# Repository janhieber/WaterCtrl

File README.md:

WaterCtrl - Automatically water your flowers

# About
This project is a complete system to automatically
water your flowers. Yes, you can eventually go to holiday after years staying at home
because of your flowers.

Currently it is under development.
- The measure boards are finished.
- The main board is is in prototype stage.
- The Webinterface is nearly finished.
- The firmware development was just startet.

The idea is to measure the moisture of your flowser soil and
water them when needed. The watering is done according to moisture
or at a specific time intervall (for cactus).

The board will have a connector for a Raspberry Pi
which takes care of all high level functions like:
WLAN/LAN connection, webinterface, watering algorithm, weather station... 

The STM32 CPU will take care of the low level functions like:
watchdog for the rPi, PWM motor control, frequency measurement.

# Design
This is my idea of the device.

And this is the hardware design.

# Technical
Measure:
The moisture measurement is done by a oscillating circuit that uses two
big copper planes as capacitor in the soil.
When the soil is wet the capacity is high and the frequency will be low.

# More details
Please look in the subfolders for more informations,
nice pictures and other stuff.

# My future plans
I have some nice ideas, let me know what you think about this:

- The rPi will become the central control device with a radio module.
- Small sensor boards with a radio can interface a few sensors.
- Small motor control boards with a radio can control a few motors.
- The rPi, sensor and motor boards can be connected with wires when you don't want/need
  radio.
- Multiple sensor and motor boards can be used with one rPi. This way
  you can scale the system like you need it.

This will allow a complete modular system with most low level functions outsourced on
smaller modules and less long wires laying around.

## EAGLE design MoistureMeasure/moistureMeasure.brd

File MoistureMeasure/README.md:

Here are the Eagle 6.x schematics and board file for
the moistue measurement.

# Notes
The gray rectangle bottom left should be cut out to stick the
cable before spilling the board with epoxy.

# Nice pictures

")

# Order PCBs
For cheap PCBs you can order here:
http://dirtypcbs.com/
or here:
http://www.elecrow.com/services-pcb-prototyping-c-73_116.html

Because most people will [have to] order 5 or 10 pieces you can ask
me if someone as some PCBs left. If you have PCBs left, please tell me via Github
or mail: mail at janhieber dot net

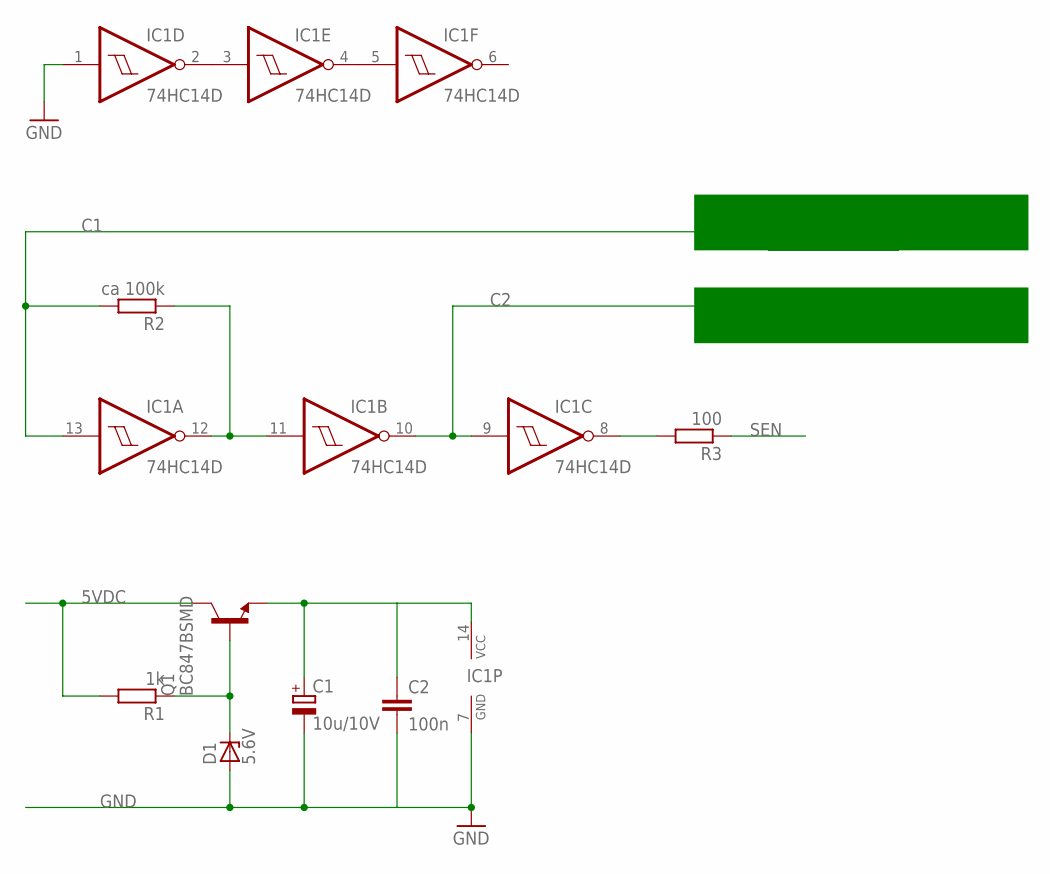
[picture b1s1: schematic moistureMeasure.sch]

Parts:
C1: 10u/10V; A/3216-18W
C2: 100n; C0805
D1: 5.6V; SOD80C
IC1: 74HC14D; SO14
Q1: BC847BSMD; SOT23
R1: 1k; R0805
R2: ca 100k; R0805
R3: 100; R0805

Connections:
5VDC: Q1.3 (C), R1.2
C1: IC1.13 (I), R2.2
C2: IC1.9 (I), IC1.10 (O)
GND: C1.-, C2.2, D1.A, IC1.1 (I), IC1.7 (GND)
unnamed: D1.C, Q1.1 (B), R1.1
unnamed: C1.+, C2.1, IC1.14 (VCC), Q1.2 (E)
unnamed: IC1.2 (O), IC1.3 (I)
unnamed: IC1.4 (O), IC1.5 (I)
unnamed: IC1.11 (I), IC1.12 (O), R2.1
unnamed: IC1.8 (O), R3.2
SEN: R3.1

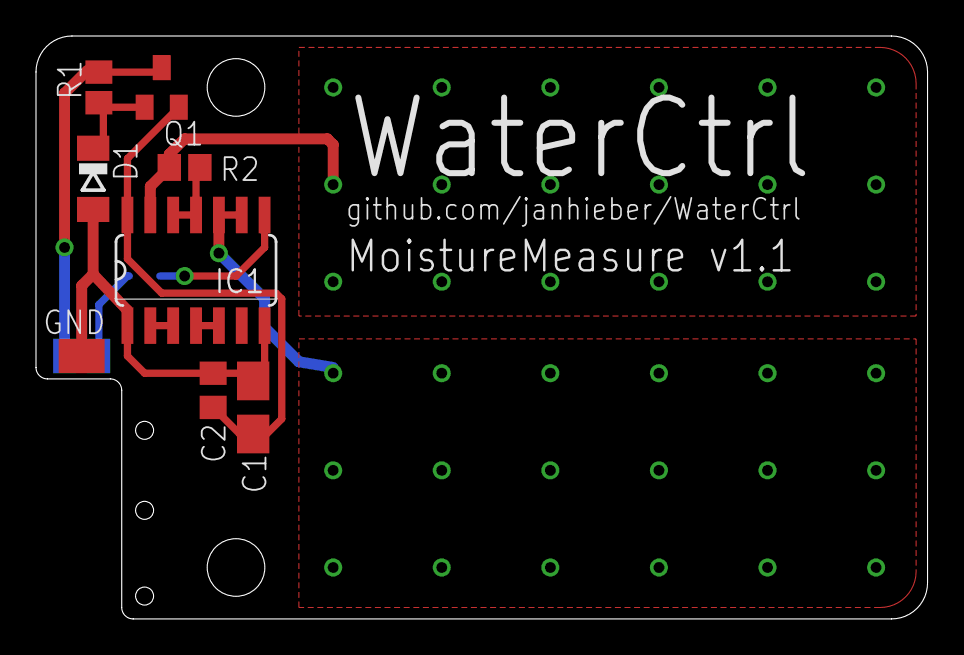
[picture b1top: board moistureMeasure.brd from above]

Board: 2 copper layers, 49.5 x 32.4 mm, 8 parts (1 on the bottom side), 10 nets.

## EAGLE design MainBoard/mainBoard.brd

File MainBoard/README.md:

News: First PCBs are ordered!

# Progress
First PCBs arrived!

# Info
This is the Eagle schematic/layout for the main board.

When I'm working on schematics or layout I'll update the
[schematic.pdf](https://github.com/janhieber/WaterCtrl/raw/master/MainBoard/docu/schematic.pdf) and
[board.png](https://github.com/janhieber/WaterCtrl/raw/master/MainBoard/docu/board.png) files.

Current layout

This is the STM32 board I have chosen for low level work.

It has a low power ARM Cortex M3 CPU running at max 72MHz.  
Should be enough for PWM and frequency measurement.  
It's very cheap (look on eBay) and has no useless peripherals.

# Order PCBs
For cheap PCBs you can order here: [http://dirtypcbs.com](http://dirtypcbs.com)

Because most people will [have to] order 5 or 10 pieces you can ask
me if someone has some PCBs left. If you have PCBs left, please tell me via Github Issue
or mail: mail at janhieber dot net

# Order parts
The parts are all from Reichelt (http://www.reichelt.de/) except the
STM32 board which I ordered on eBay.

Every part in the schematic has an attribute "R" with the Reichelt
part number as value.

To generate the BOM do the following:
 1. Open the schematic in Eagle
 2. File > Export > BOM
 3. Select "values" as list type

Now, Reichelt expects a CSV file with the following format:  
> DIODE GN;2  
> SMD 0805 100K;12

If you are working on Linux or Mac OSX you can execute this in a terminal:  
```bash
tail -n +2 BOM.csv | sed 's/\"//g' | awk -F ';' 'length($11)>0{print $11";"$1}' > BOM_reichelt.csv
```

*make sure you are in the directory where the BOM.csv is*

Otherwise use Libreoffice or Excel etc to generate the list, or add everything
manually to cart.

Now register at Reichelt and login.  
Click on your username on top and then "load cart" to import the CSV.

# ToDo
- [ ] Circuit for the moisture measurement (connectors, demultiplexer)
  - [x] schematic
  - [x] routed
  - [ ] tested
- [ ] Circuit for the water pump controlling (FETs ...)
  - [x] schematic
  - [x] routed
  - [ ] tested
- [x] Power supply circuit for 5V
  - [x] schematic
  - [x] routed
  - [x] tested
- [ ] Wiring up the STM32 and rPi
  - [x] schematic
  - [x] routed
  - [ ] SPI connection
  - [ ] tested

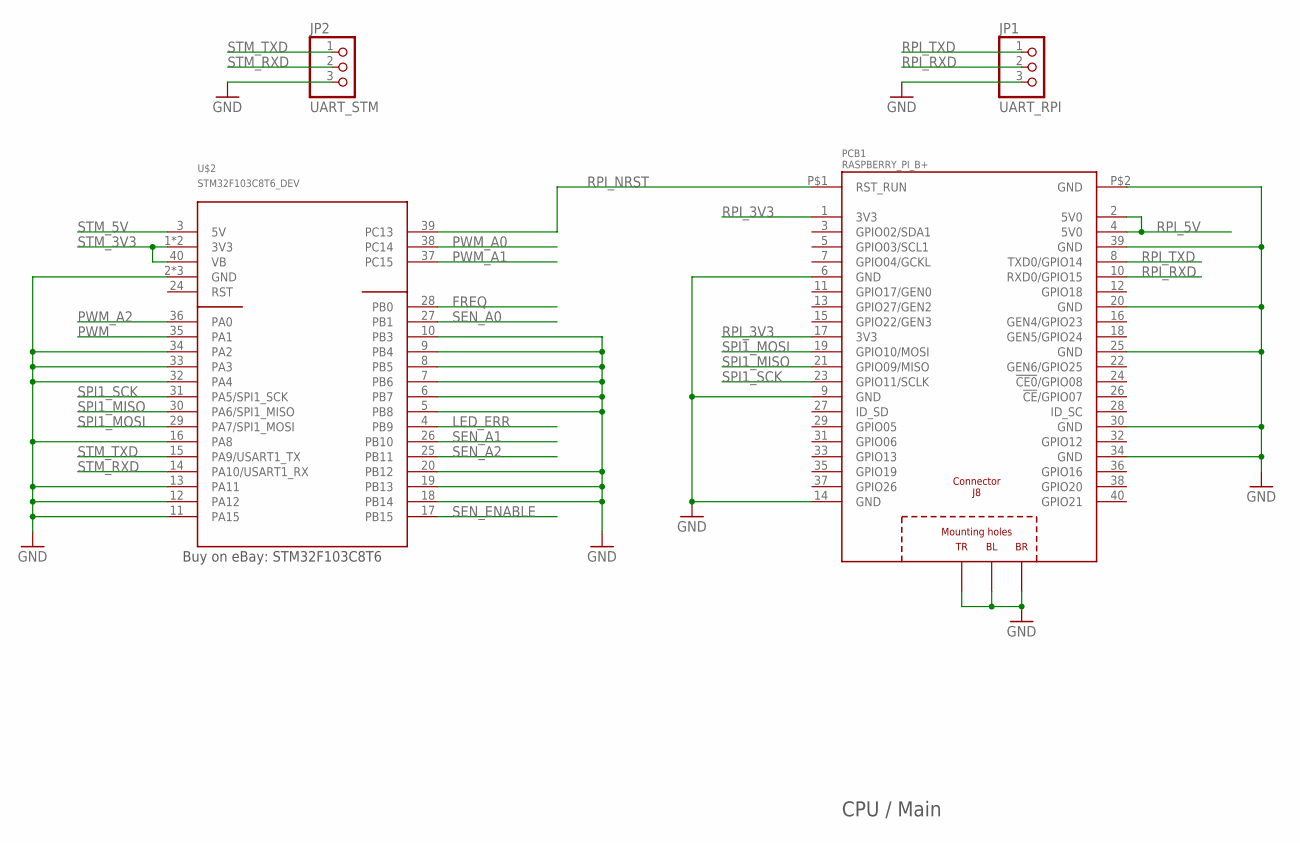
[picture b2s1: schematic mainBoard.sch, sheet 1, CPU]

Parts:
JP1: UART_RPI; 1X03
JP2: UART_STM; 1X03
PCB1: RASPBERRY_PI_B+; RASPBERRY_PI_BPLUS_TPLACE_SMD_MIRR
U$2: STM32F103C8T6_DEV; STM32F103C8T6_DEV_SMD

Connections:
FREQ: U$2.28 (PB0); also elsewhere on the board
GND: JP1.3, JP2.3, PCB1.6 (GND), PCB1.9 (GND), PCB1.14 (GND), PCB1.20 (GND), PCB1.25 (GND), PCB1.30 (GND), PCB1.34 (GND), PCB1.39 (GND), PCB1.P$2 (GND), PCB1.PE_BL (BL), PCB1.PE_BR (BR), PCB1.PE_TR (TR), U$2.2 (GND), U$2.5 (PB8), U$2.6 (PB7), U$2.7 (PB6), U$2.8 (PB5), U$2.9 (PB4), U$2.10 (PB3), U$2.11 (PA15), U$2.12 (PA12), U$2.13 (PA11), U$2.16 (PA8), U$2.18 (PB14), U$2.19 (PB13), U$2.20 (PB12), U$2.21 (GND), U$2.22 (GND), U$2.32 (PA4), U$2.33 (PA3), U$2.34 (PA2); also elsewhere on the board
LED_ERR: U$2.4 (PB9); also elsewhere on the board
PWM: U$2.35 (PA1); also elsewhere on the board
PWM_A0: U$2.38 (PC14); also elsewhere on the board
PWM_A1: U$2.37 (PC15); also elsewhere on the board
PWM_A2: U$2.36 (PA0); also elsewhere on the board
RPI_3V3: PCB1.1 (3V3), PCB1.17 (3V3); also elsewhere on the board
RPI_5V: PCB1.2 (5V0), PCB1.4 (5V0); also elsewhere on the board
RPI_NRST: PCB1.P$1 (RST_RUN), U$2.39 (PC13)
RPI_RXD: JP1.2, PCB1.10 (RXD0/GPIO15)
RPI_TXD: JP1.1, PCB1.8 (TXD0/GPIO14)
SEN_A0: U$2.27 (PB1); also elsewhere on the board
SEN_A1: U$2.26 (PB10); also elsewhere on the board
SEN_A2: U$2.25 (PB11); also elsewhere on the board
SEN_ENABLE: U$2.17 (PB15); also elsewhere on the board
SPI1_MISO: PCB1.21 (GPIO09/MISO), U$2.30 (PA6/SPI1_MISO)
SPI1_MOSI: PCB1.19 (GPIO10/MOSI), U$2.29 (PA7/SPI1_MOSI)
SPI1_SCK: PCB1.23 (GPIO11/SCLK), U$2.31 (PA5/SPI1_SCK)
STM_3V3: U$2.1 (3V3), U$2.23 (3V3), U$2.40 (VB); also elsewhere on the board
STM_5V: U$2.3 (5V); also elsewhere on the board
STM_RXD: JP2.2, U$2.14 (PA10/USART1_RX)
STM_TXD: JP2.1, U$2.15 (PA9/USART1_TX)

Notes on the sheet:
CPU / Main
Buy on eBay: STM32F103C8T6

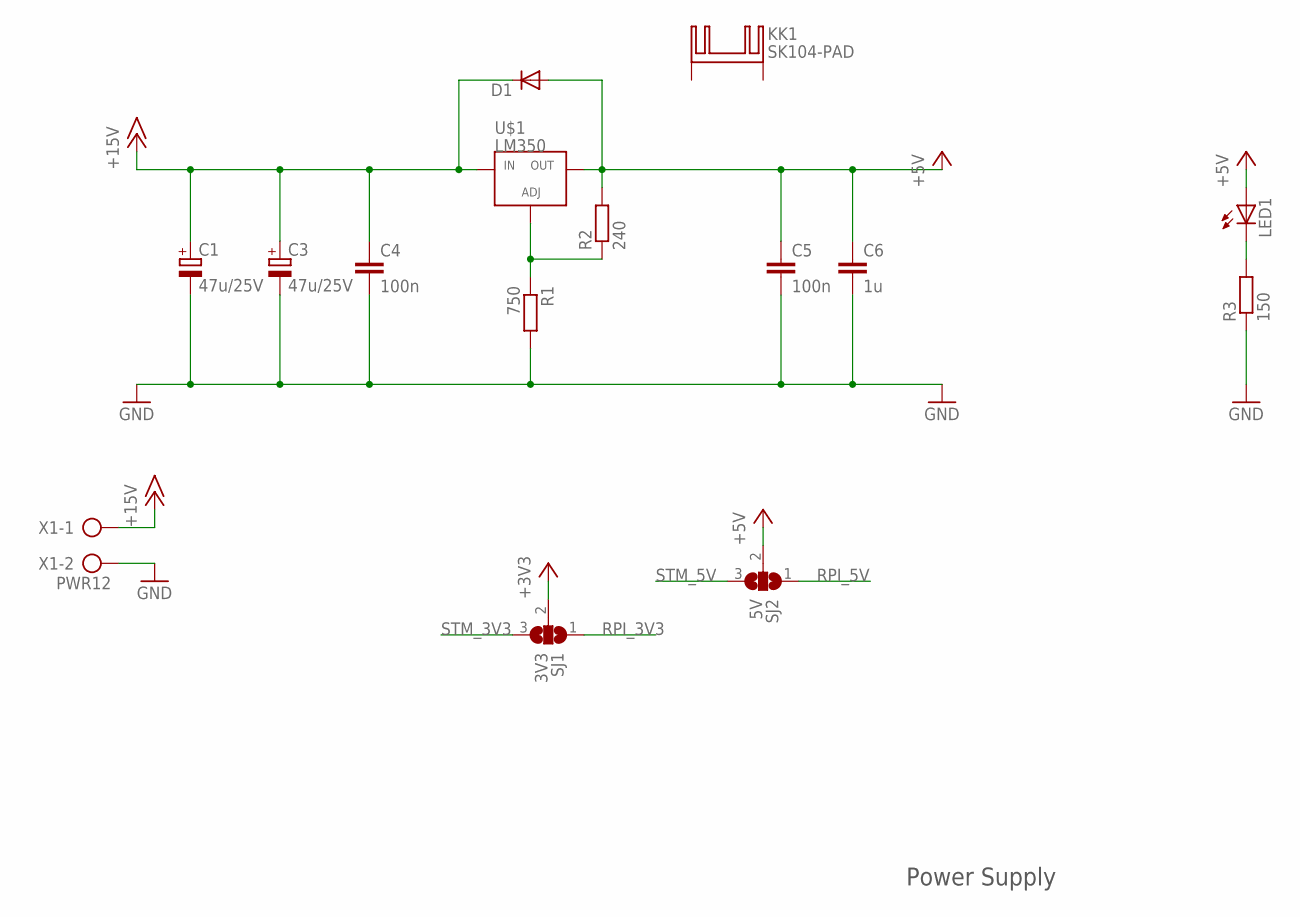
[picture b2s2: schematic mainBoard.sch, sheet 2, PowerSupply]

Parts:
C1, C3: 47u/25V; PANASONIC_D
C4, C5: 100n; C0805
C6: 1u; C0805
D1: DIODE-MELF-MLL41; MELF-MLL41
KK1: SK104-PAD
LED1: LEDCHIP-LED0805; CHIP-LED0805
R1: 750; R0805
R2: 240; R0805
R3: 150; R0805
SJ1: 3V3; SJ_2
SJ2: 5V; SJ_2
U$1: LM350; TO220
X1: PWR12; AK500/2

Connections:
+3V3: SJ1.2; also elsewhere on the board
+5V: C5.1, C6.1, D1.A, LED1.A, R2.2, SJ2.2, U$1.2 (OUT)
+15V: C1.+, C3.+, C4.1, D1.C, U$1.3 (IN), X1.1; also elsewhere on the board
GND: C1.-, C3.-, C4.2, C5.2, C6.2, R1.2, R3.1, X1.2; also elsewhere on the board
unnamed: LED1.C, R3.2
unnamed: R1.1, R2.1, U$1.1 (ADJ)
RPI_3V3: SJ1.1; also elsewhere on the board
RPI_5V: SJ2.1; also elsewhere on the board
STM_3V3: SJ1.3; also elsewhere on the board
STM_5V: SJ2.3; also elsewhere on the board

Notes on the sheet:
Power Supply

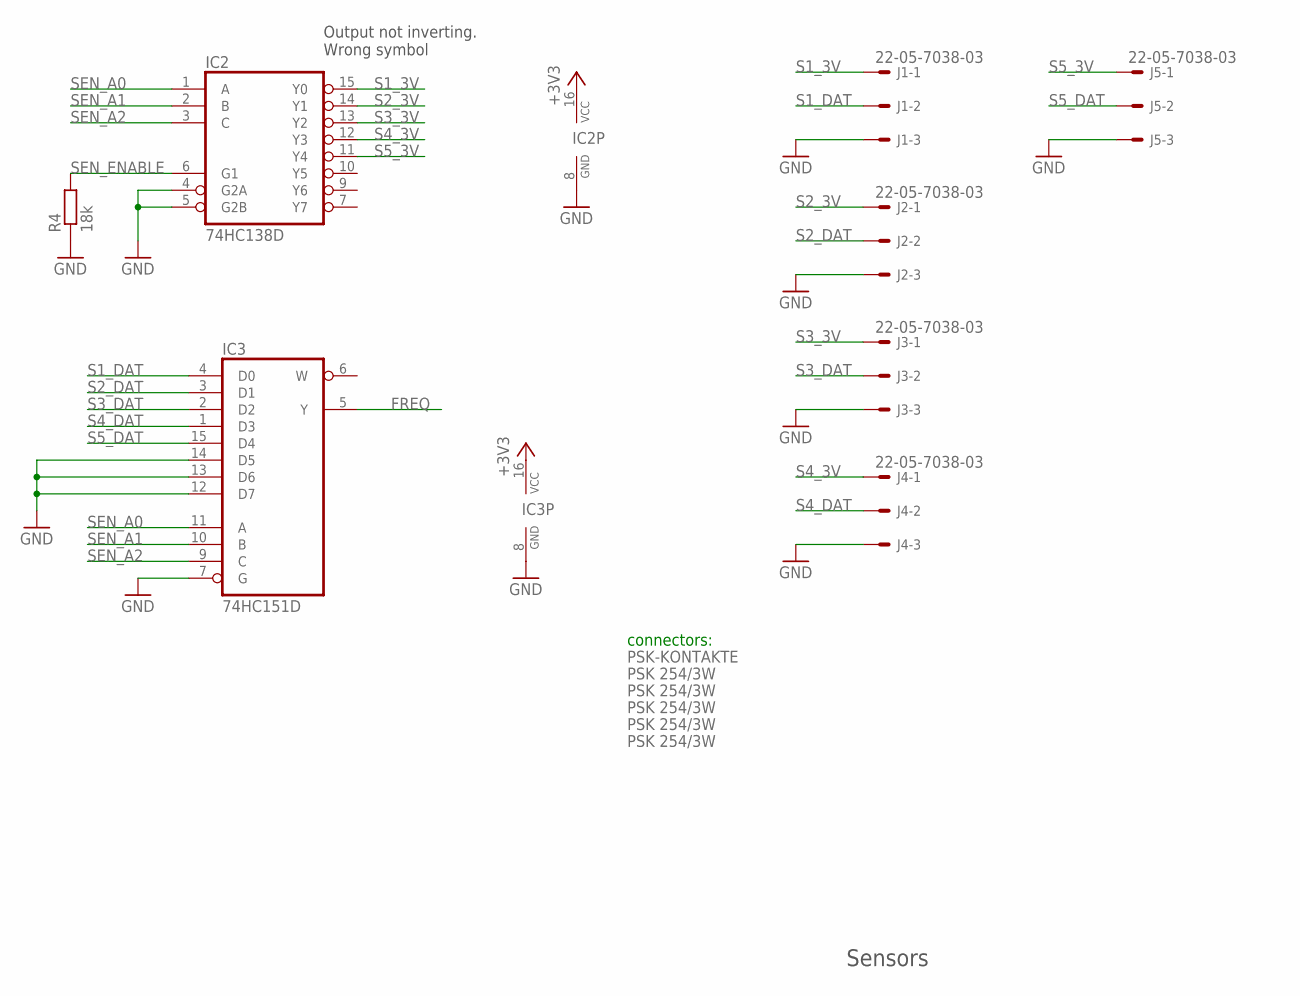
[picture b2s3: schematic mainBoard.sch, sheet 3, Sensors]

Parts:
IC2: 74HC138D; SO16
IC3: 74HC151D; SO16
J1, J2, J3, J4, J5: 22-05-7038-03; 7395-03
R4: 18k; R0805
U$3, U$4, U$5, U$6, U$7: PSK 254/3W; DUMMY_BOM
U$8: PSK-KONTAKTE; DUMMY_BOM

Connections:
+3V3: IC2.16 (VCC), IC3.16 (VCC); also elsewhere on the board
FREQ: IC3.5 (Y); also elsewhere on the board
GND: IC2.4 (G2A), IC2.5 (G2B), IC2.8 (GND), IC3.7 (G), IC3.8 (GND), IC3.12 (D7), IC3.13 (D6), IC3.14 (D5), J1.3, J2.3, J3.3, J4.3, J5.3, R4.1; also elsewhere on the board
S1_3V: IC2.15 (Y0), J1.1
S1_DAT: IC3.4 (D0), J1.2
S2_3V: IC2.14 (Y1), J2.1
S2_DAT: IC3.3 (D1), J2.2
S3_3V: IC2.13 (Y2), J3.1
S3_DAT: IC3.2 (D2), J3.2
S4_3V: IC2.12 (Y3), J4.1
S4_DAT: IC3.1 (D3), J4.2
S5_3V: IC2.11 (Y4), J5.1
S5_DAT: IC3.15 (D4), J5.2
SEN_A0: IC2.1 (A), IC3.11 (A); also elsewhere on the board
SEN_A1: IC2.2 (B), IC3.10 (B); also elsewhere on the board
SEN_A2: IC2.3 (C), IC3.9 (C); also elsewhere on the board
SEN_ENABLE: IC2.6 (G1), R4.2; also elsewhere on the board

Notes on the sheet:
Output not inverting. Wrong symbol
connectors:
Sensors

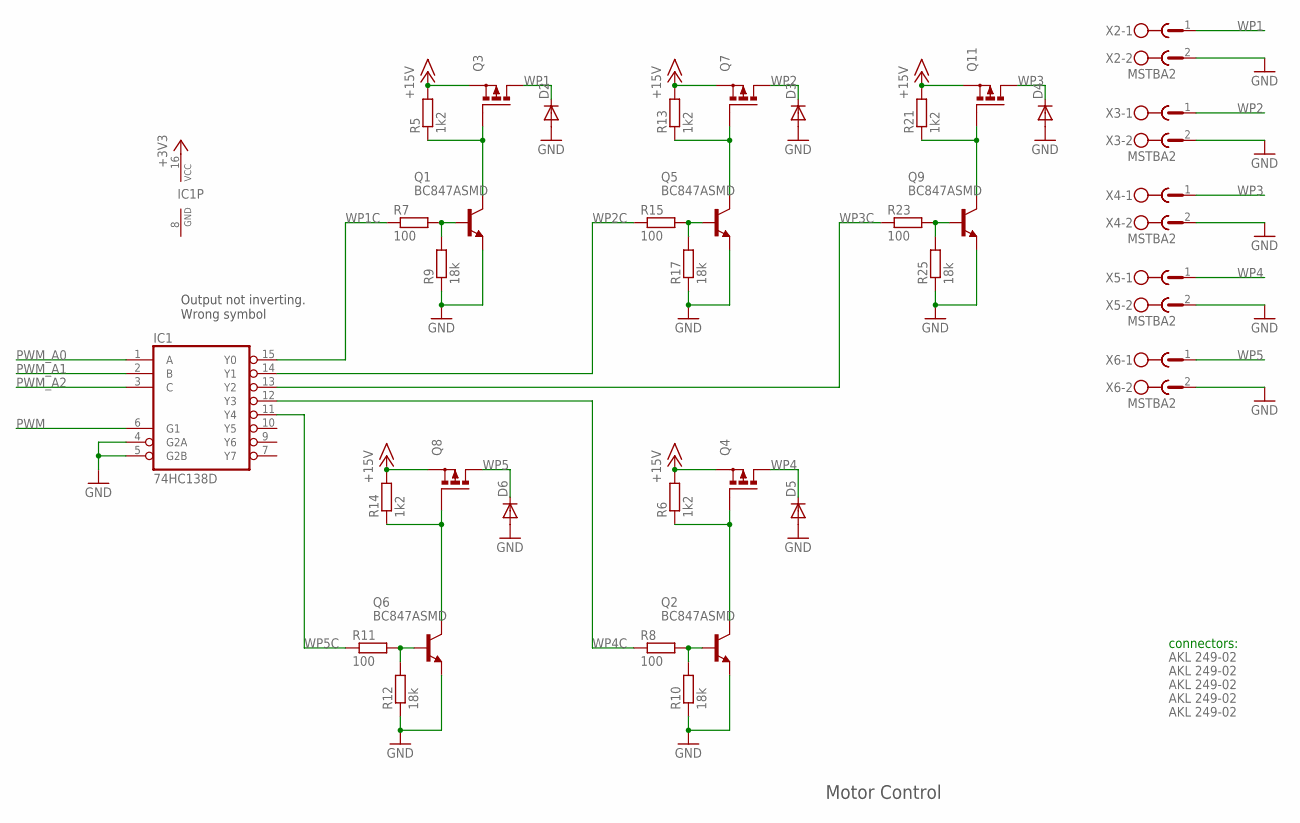
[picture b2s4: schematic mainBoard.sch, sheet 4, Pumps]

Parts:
D2, D3, D4, D5, D6: DIODE-DO-214AC; DO-214AC
IC1: 74HC138D; SO16
Q1, Q2, Q5, Q6, Q9: BC847ASMD; SOT23
Q3, Q4, Q7, Q8, Q11: P-MOSFET-SO8; SO-08
R5, R6, R13, R14, R21: 1k2; R0805
R7, R8, R11, R15, R23: 100; R0805
R9, R10, R12, R17, R25: 18k; R0805
U$9, U$10, U$11, U$12, U$13: AKL 249-02; DUMMY_BOM
X2, X3, X4, X5, X6: MSTBA2

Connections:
+3V3: IC1.16 (VCC); also elsewhere on the board
+15V: Q3.1 (S), Q3.2 (S), Q3.3 (S), Q4.1 (S), Q4.2 (S), Q4.3 (S), Q7.1 (S), Q7.2 (S), Q7.3 (S), Q8.1 (S), Q8.2 (S), Q8.3 (S), Q11.1 (S), Q11.2 (S), Q11.3 (S), R5.2, R6.2, R13.2, R14.2, R21.2; also elsewhere on the board
GND: D2.A, D3.A, D4.A, D5.A, D6.A, IC1.4 (G2A), IC1.5 (G2B), IC1.8 (GND), Q1.2 (E), Q2.2 (E), Q5.2 (E), Q6.2 (E), Q9.2 (E), R9.1, R10.1, R12.1, R17.1, R25.1, X2.2, X3.2, X4.2, X5.2, X6.2; also elsewhere on the board
unnamed: Q5.3 (C), Q7.4 (G), R13.1
unnamed: Q1.3 (C), Q3.4 (G), R5.1
unnamed: Q6.3 (C), Q8.4 (G), R14.1
unnamed: Q1.1 (B), R7.2, R9.2
unnamed: Q6.1 (B), R11.2, R12.2
unnamed: Q5.1 (B), R15.2, R17.2
unnamed: Q9.3 (C), Q11.4 (G), R21.1
unnamed: Q9.1 (B), R23.2, R25.2
unnamed: Q2.3 (C), Q4.4 (G), R6.1
unnamed: Q2.1 (B), R8.2, R10.2
PWM: IC1.6 (G1); also elsewhere on the board
PWM_A0: IC1.1 (A); also elsewhere on the board
PWM_A1: IC1.2 (B); also elsewhere on the board
PWM_A2: IC1.3 (C); also elsewhere on the board
WP1: D2.C, Q3.5 (D), Q3.6 (D), Q3.7 (D), Q3.8 (D), X2.1
WP1C: IC1.15 (Y0), R7.1
WP2: D3.C, Q7.5 (D), Q7.6 (D), Q7.7 (D), Q7.8 (D), X3.1
WP2C: IC1.14 (Y1), R15.1
WP3: D4.C, Q11.5 (D), Q11.6 (D), Q11.7 (D), Q11.8 (D), X4.1
WP3C: IC1.13 (Y2), R23.1
WP4: D5.C, Q4.5 (D), Q4.6 (D), Q4.7 (D), Q4.8 (D), X5.1
WP4C: IC1.12 (Y3), R8.1
WP5: D6.C, Q8.5 (D), Q8.6 (D), Q8.7 (D), Q8.8 (D), X6.1
WP5C: IC1.11 (Y4), R11.1

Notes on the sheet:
Motor Control
connectors:
Output not inverting. Wrong symbol

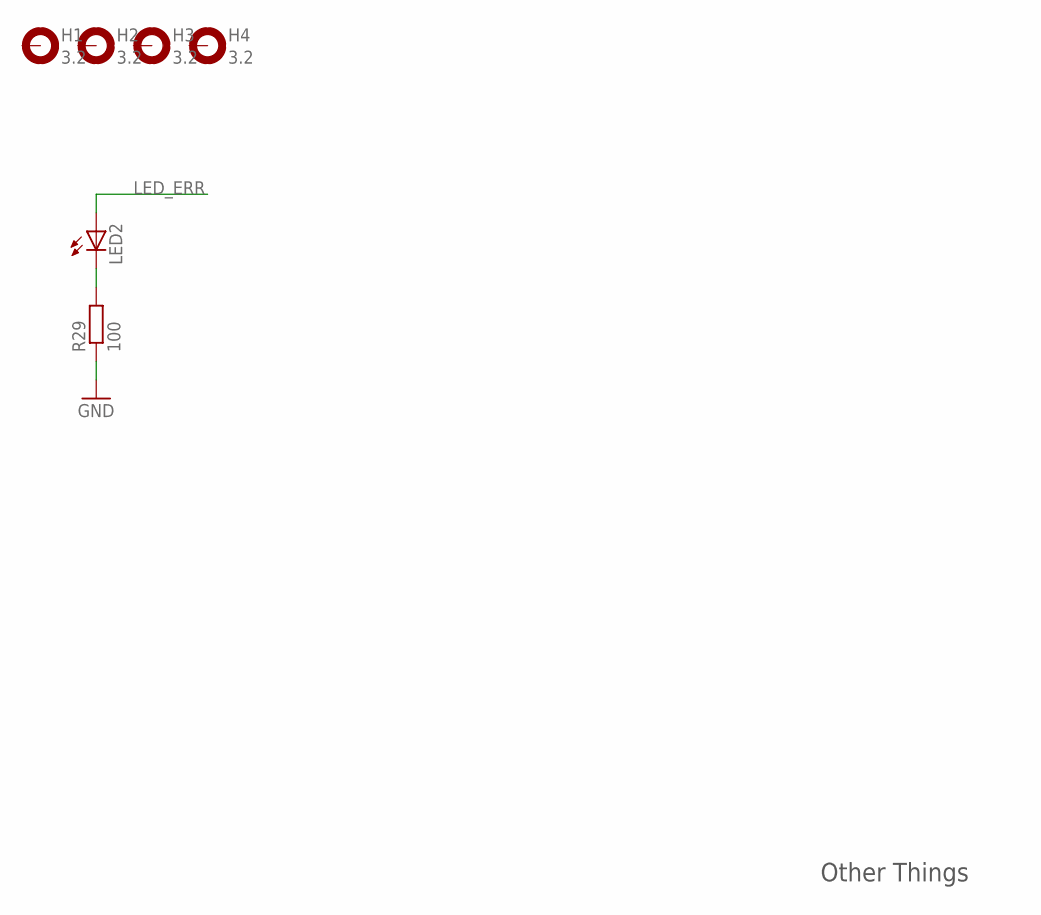
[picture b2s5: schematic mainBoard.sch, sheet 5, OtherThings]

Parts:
H1, H2, H3, H4: 3.2; 3,2-PAD
LED2: LED3MM
R29: 100; R0805

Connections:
GND: R29.1; also elsewhere on the board
LED_ERR: LED2.A; also elsewhere on the board
unnamed: LED2.K (C), R29.2

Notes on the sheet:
Other Things

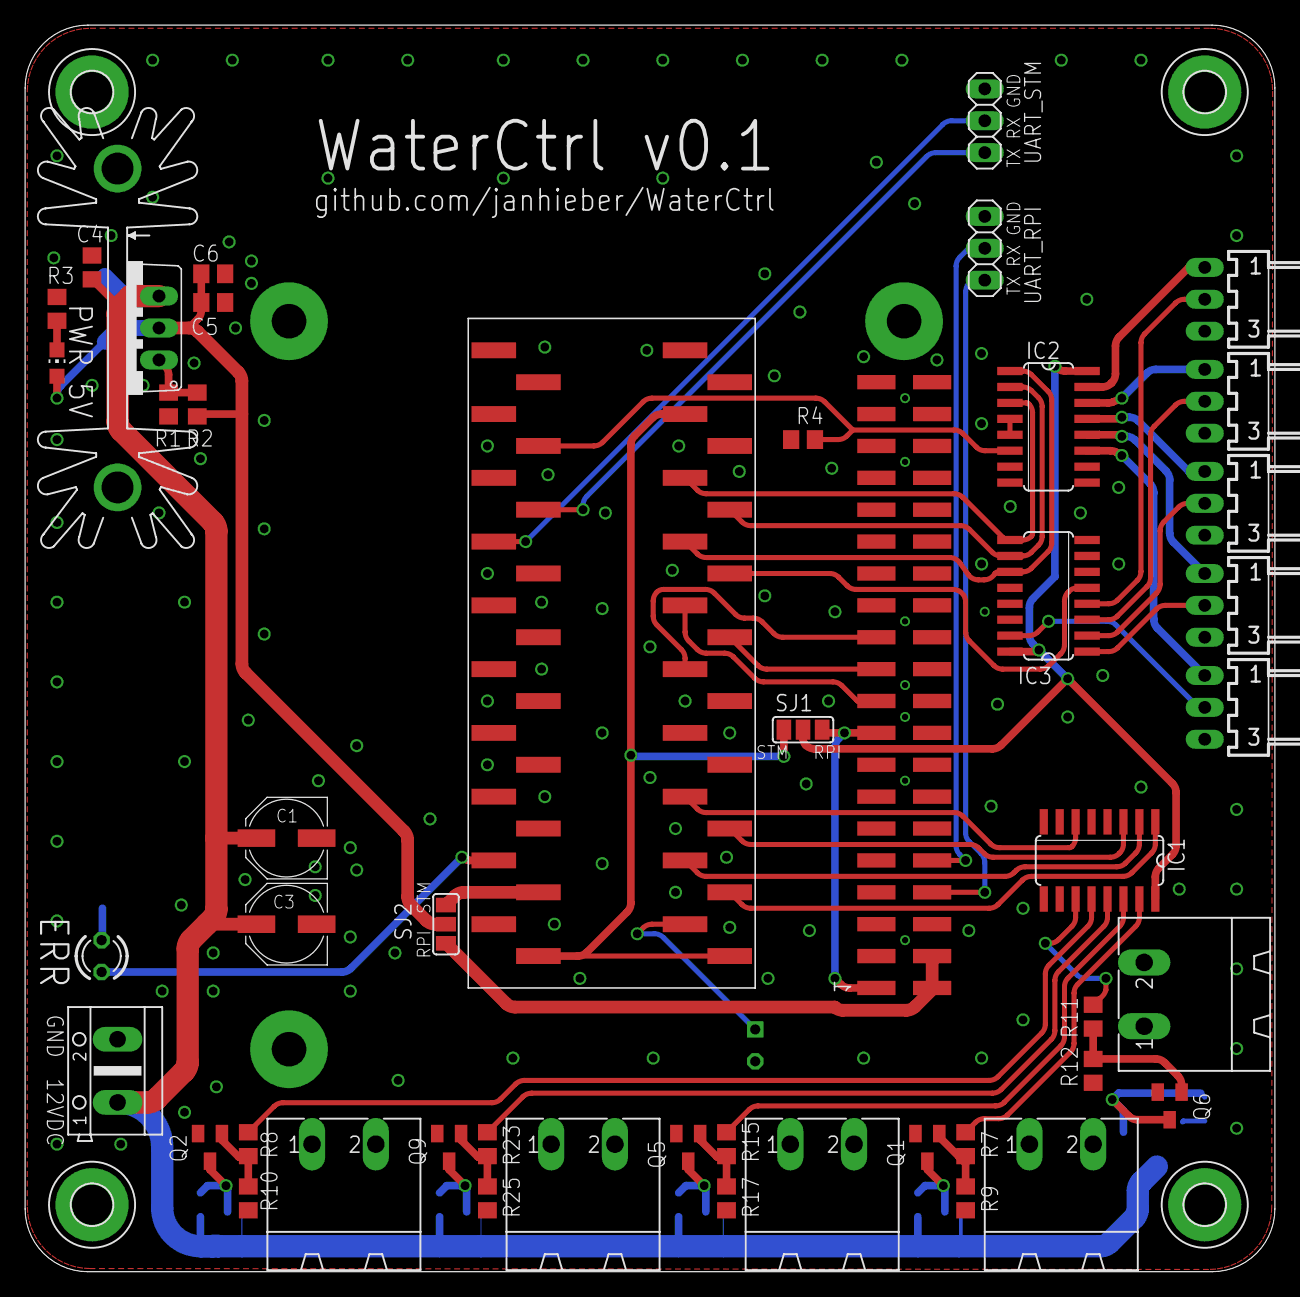
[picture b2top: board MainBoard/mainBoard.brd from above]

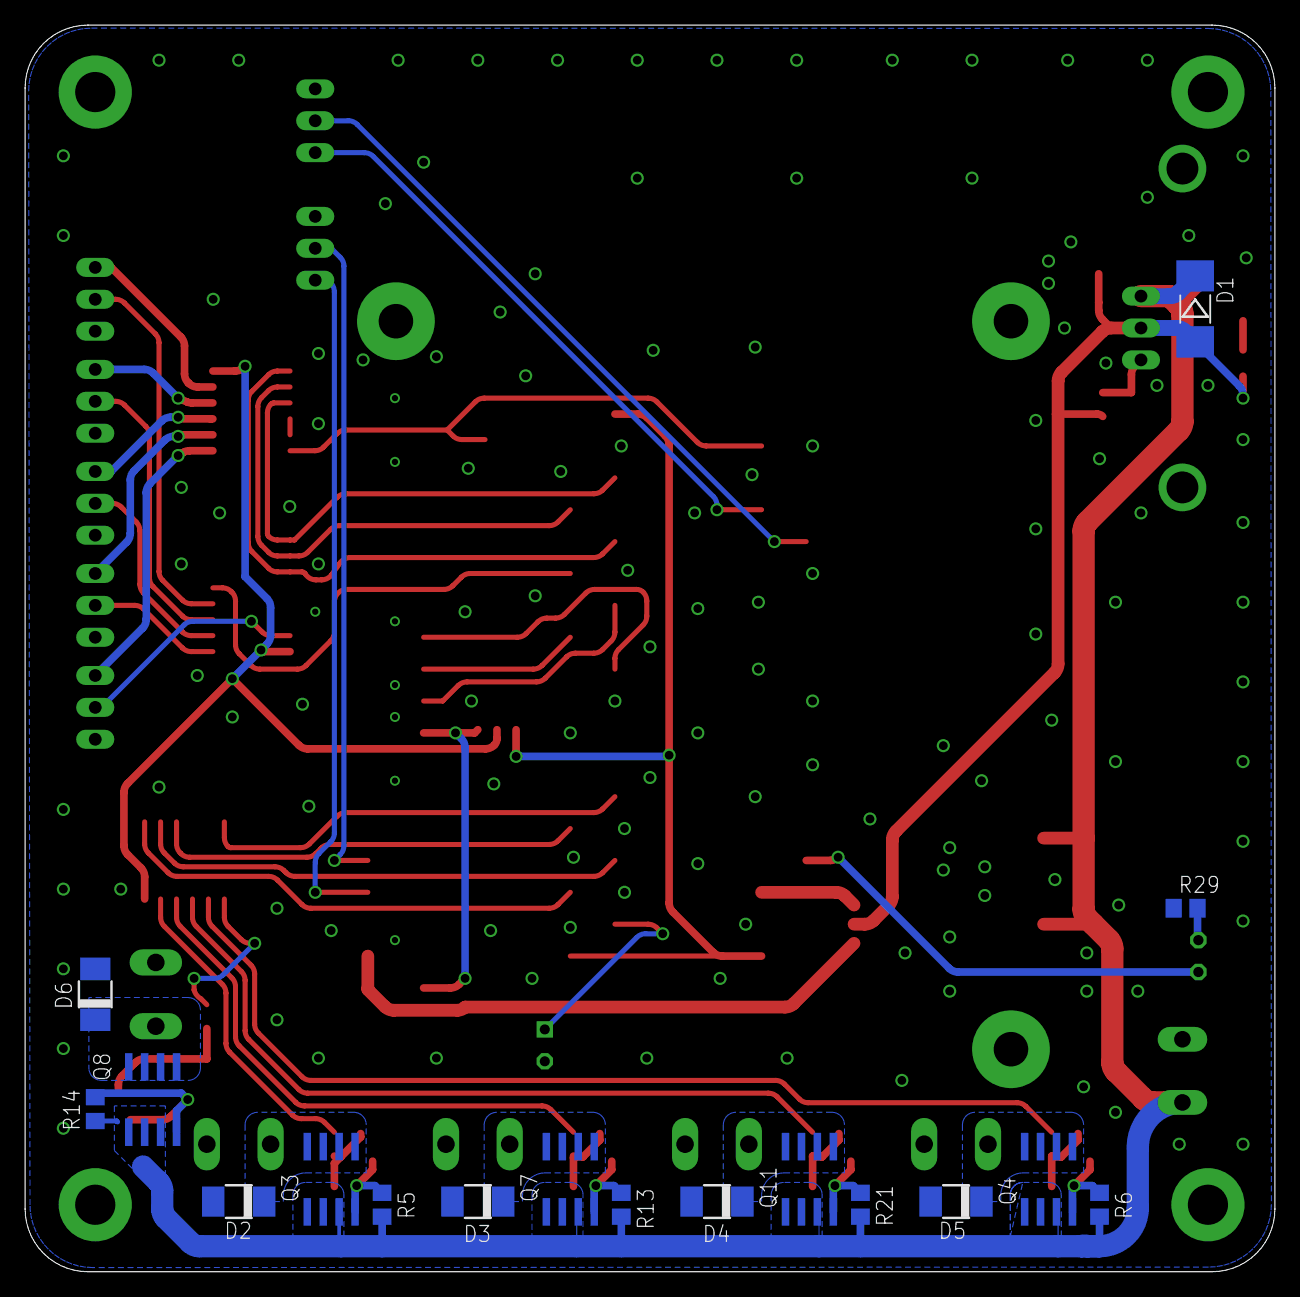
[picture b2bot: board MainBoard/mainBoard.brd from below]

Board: 2 copper layers, 99.6 x 99.3 mm, 80 parts (17 on the bottom side), 59 nets.

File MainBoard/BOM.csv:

"Qty";"Value";"Device";"Package";"Parts";"Description";"MF";"MPN";"OC_FARNELL";"OC_NEWARK";"R";
"5";"";"DIODE-DO-214AC";"DO-214AC";"D2, D3, D4, D5, D6";"DIODE";"";"";"";"";"B 140 F";
"1";"";"DIODE-MELF-MLL41";"MELF-MLL41";"D1";"DIODE";"";"";"";"";"1N 4002 SMD";
"1";"";"LED3MM";"LED3MM";"LED2";"LED";"";"";"";"";"SLK 3MM RT";
"1";"";"LEDCHIP-LED0805";"CHIP-LED0805";"LED1";"LED";"";"";"";"";"SMD-LED 0805 GN";
"5";"";"P-MOSFET-SO8";"SO-08";"Q3, Q4, Q7, Q8, Q11";"P-Channel MOSFET";"";"";"";"";"IRF 9332";
"6";"100";"R-EU_R0805";"R0805";"R7, R8, R11, R15, R23, R29";"RESISTOR, European symbol";"";"";"";"";"SMD-0805 100";
"2";"100n";"C-EUC0805";"C0805";"C4, C5";"CAPACITOR, European symbol";"";"";"";"";"X7R-G0805 100N";
"1";"150";"R-EU_R0805";"R0805";"R3";"RESISTOR, European symbol";"";"";"";"";"SMD-0805 150";
"6";"18k";"R-EU_R0805";"R0805";"R4, R9, R10, R12, R17, R25";"RESISTOR, European symbol";"";"";"";"";"SMD-0805 18,0K";
"5";"1k2";"R-EU_R0805";"R0805";"R5, R6, R13, R14, R21";"RESISTOR, European symbol";"";"";"";"";"SMD-0805 1,20K";
"1";"1u";"C-EUC0805";"C0805";"C6";"CAPACITOR, European symbol";"";"";"";"";"X7R-G0805 1,0/25";
"5";"22-05-7038-03";"22-05-7038-03";"7395-03";"J1, J2, J3, J4, J5";"CONNECTOR";"";"";"unknown";"unknown";"PSS 254/3W";
"1";"240";"R-EU_R0805";"R0805";"R2";"RESISTOR, European symbol";"";"";"";"";"SPR-0805 240";
"4";"3.2";"MOUNT-PAD-ROUND3.2";"3,2-PAD";"H1, H2, H3, H4";"MOUNTING PAD, round";"";"";"";"";"";
"1";"3V3";"SJ2W";"SJ_2";"SJ1";"SMD solder JUMPER";"";"";"";"";"";
"2";"47u/25V";"CPOL-EUD";"PANASONIC_D";"C1, C3";"POLARIZED CAPACITOR, European symbol";"";"";"";"";"VF 47/25 P-D";
"1";"5V";"SJ2W";"SJ_2";"SJ2";"SMD solder JUMPER";"";"";"";"";"";
"2";"74HC138D";"74HC138D";"SO16";"IC1, IC2";"3-line to 8-line DECODER/DEMULTIPLEXER";"";"";"";"";"SMD HC 238";
"1";"74HC151D";"74HC151D";"SO16";"IC3";"Data SELECTOR/MULTIPLEXER";"";"";"";"";"SMD HC 151";
"1";"750";"R-EU_R0805";"R0805";"R1";"RESISTOR, European symbol";"";"";"";"";"SPR-0805 750";
"5";"AKL 249-02";"DUMMY_BOM";"DUMMY_BOM";"U$9, U$10, U$11, U$12, U$13";"";"";"";"";"";"AKL 249-02";
"5";"BC847ASMD";"BC847ASMD";"SOT23";"Q1, Q2, Q5, Q6, Q9";"NPN Transistor";"";"";"";"";"BC 847A SMD";
"1";"LM350";"LM350";"TO220";"U$1";"";"";"";"";"";"LM 350-220";
"5";"MSTBA2";"MSTBA2";"MSTBA2";"X2, X3, X4, X5, X6";"PHOENIX";"FARNELL";"1757242";"3705171";"71C4161";"AKL 230-02";
"5";"PSK 254/3W";"DUMMY_BOM";"DUMMY_BOM";"U$3, U$4, U$5, U$6, U$7";"";"";"";"";"";"PSK 254/3W";
"1";"PSK-KONTAKTE";"DUMMY_BOM";"DUMMY_BOM";"U$8";"";"";"";"";"";"PSK-KONTAKTE";
"1";"PWR12";"AK500/2";"AK500/2";"X1";"CONNECTOR";"";"";"unknown";"unknown";"AKL 101-02";
"1";"RASPBERRY_PI_B+";"RASPBERRY_PI_B+";"RASPBERRY_PI_BPLUS_TPLACE_SMD_MIRR";"PCB1";"Raspberry Pi B+";"";"";"";"";"";
"1";"SK104-PAD";"SK104-PAD";"SK104-PAD";"KK1";"HEATSINK manufacturer Fischer/distributor Buerklin";"";"";"";"";"";
"1";"STM32F103C8T6_DEV";"STM32F103C8T6_DEV";"STM32F103C8T6_DEV_SMD";"U$2";"";"";"";"";"";"";
"1";"UART_RPI";"PINHD-1X3";"1X03";"JP1";"PIN HEADER";"";"";"";"";"MPE 087-1-003";
"1";"UART_STM";"PINHD-1X3";"1X03";"JP2";"PIN HEADER";"";"";"";"";"MPE 087-1-003";

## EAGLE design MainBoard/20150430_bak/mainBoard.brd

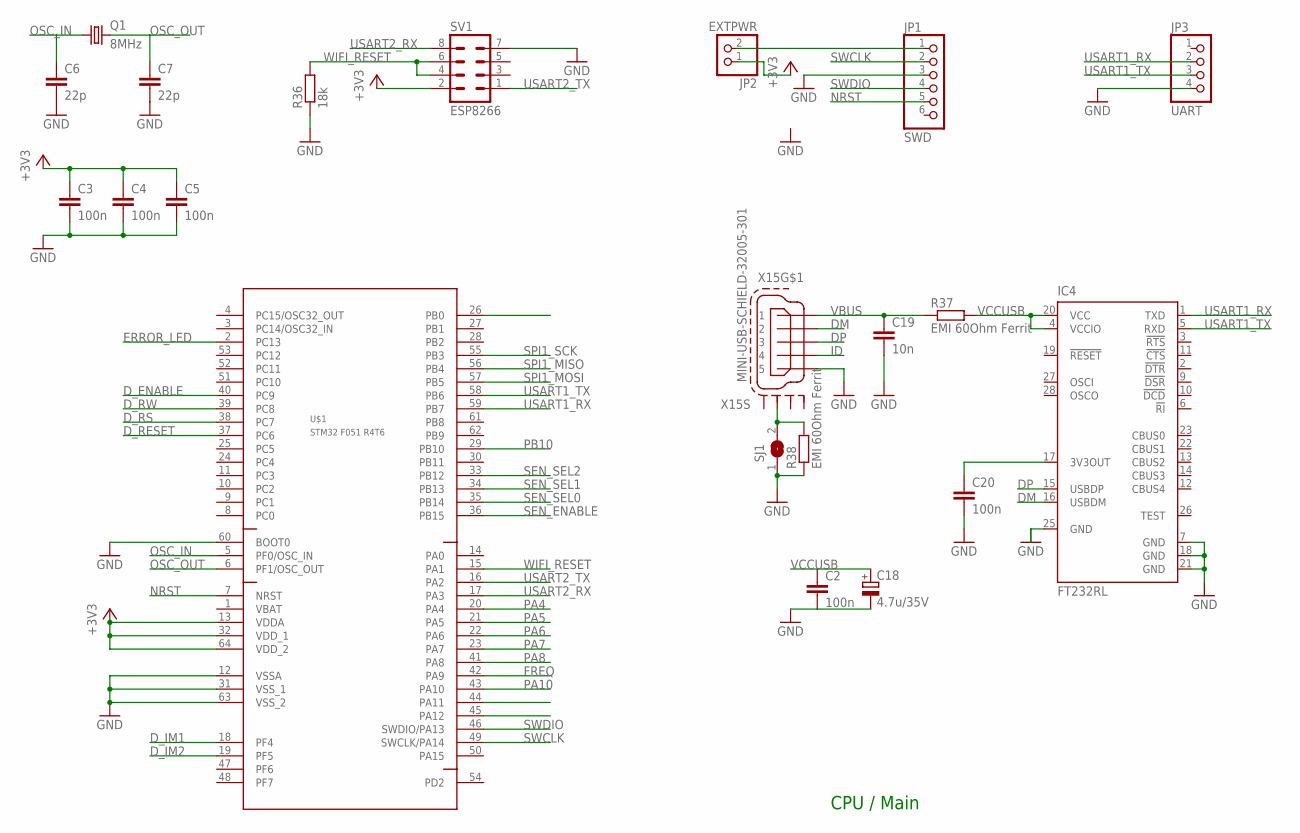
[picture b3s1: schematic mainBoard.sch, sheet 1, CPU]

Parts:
C2, C3, C4, C5, C20: 100n; C0603K
C6, C7: 22p; C0805
C18: 4.7u/35V; PANASONIC_B
C19: 10n; C0603K
IC4: FT232RL; SSOP28
JP1: SWD; 1X06
JP2: EXTPWR; 1X02
JP3: UART; 1X04
Q1: 8MHz; HC49UP
R36: 18k; R0805
R37, R38: EMI 60Ohm Ferrit; R0603
SJ1: SJ
SV1: ESP8266; MA04-2
U$1: STM32 F051 R4T6; LQFP64
X15: MINI-USB-SCHIELD-32005-301; 32005-301

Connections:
+3V3: C3.1, C4.1, C5.1, JP2.1, SV1.2, U$1.13 (VDDA), U$1.32 (VDD_1), U$1.64 (VDD_2); also elsewhere on the board
DM: IC4.16 (USBDM), X15.2
DP: IC4.15 (USBDP), X15.3
D_ENABLE: U$1.40 (PC9); also elsewhere on the board
D_IM1: U$1.18 (PF4); also elsewhere on the board
D_IM2: U$1.19 (PF5); also elsewhere on the board
D_RESET: U$1.37 (PC6); also elsewhere on the board
D_RS: U$1.38 (PC7); also elsewhere on the board
D_RW: U$1.39 (PC8); also elsewhere on the board
ERROR_LED: U$1.2 (PC13); also elsewhere on the board
FREQ: U$1.42 (PA9); also elsewhere on the board
GND: C2.2, C3.2, C4.2, C5.2, C6.2, C7.2, C18.-, C19.2, C20.2, IC4.7 (GND), IC4.18 (GND), IC4.21 (GND), IC4.25 (GND), JP1.3, JP3.4, R36.1, R38.1, SJ1.1, SV1.7, U$1.12 (VSSA), U$1.31 (VSS_1), U$1.60 (BOOT0), U$1.63 (VSS_2), X15.5; also elsewhere on the board
ID: X15.4
unnamed: JP1.1, JP2.2
unnamed: R38.2, SJ1.2, X15.M3 (S3)
unnamed: C20.1, IC4.17 (3V3OUT)
NRST: JP1.5, U$1.7 (NRST)
OSC_IN: C6.1, Q1.1, U$1.5 (PF0/OSC_IN)
OSC_OUT: C7.1, Q1.2, U$1.6 (PF1/OSC_OUT)
PA4: U$1.20 (PA4); also elsewhere on the board
PA5: U$1.21 (PA5)
PA6: U$1.22 (PA6); also elsewhere on the board
PA7: U$1.23 (PA7); also elsewhere on the board
PA8: U$1.41 (PA8); also elsewhere on the board
PA10: U$1.43 (PA10)
PB0: U$1.26 (PB0); also elsewhere on the board
PB10: U$1.29 (PB10); also elsewhere on the board
SEN_ENABLE: U$1.36 (PB15); also elsewhere on the board
SEN_SEL0: U$1.35 (PB14); also elsewhere on the board
SEN_SEL1: U$1.34 (PB13); also elsewhere on the board
SEN_SEL2: U$1.33 (PB12); also elsewhere on the board
SPI1_MISO: U$1.56 (PB4); also elsewhere on the board
SPI1_MOSI: U$1.57 (PB5); also elsewhere on the board
SPI1_SCK: U$1.55 (PB3); also elsewhere on the board
SWCLK: JP1.2, U$1.49 (SWCLK/PA14)
SWDIO: JP1.4, U$1.46 (SWDIO/PA13)
USART1_RX: IC4.1 (TXD), JP3.2, U$1.59 (PB7)
USART1_TX: IC4.5 (RXD), JP3.3, U$1.58 (PB6)
USART2_RX: SV1.8, U$1.17 (PA3)
USART2_TX: SV1.1, U$1.16 (PA2)
VBAT: U$1.1 (VBAT)
VBUS: C19.1, R37.1, X15.1
VCCUSB: C2.1, C18.+, IC4.4 (VCCIO), IC4.20 (VCC), R37.2
WIFI_RESET: R36.2, SV1.4, SV1.6, U$1.15 (PA1)

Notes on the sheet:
CPU / Main

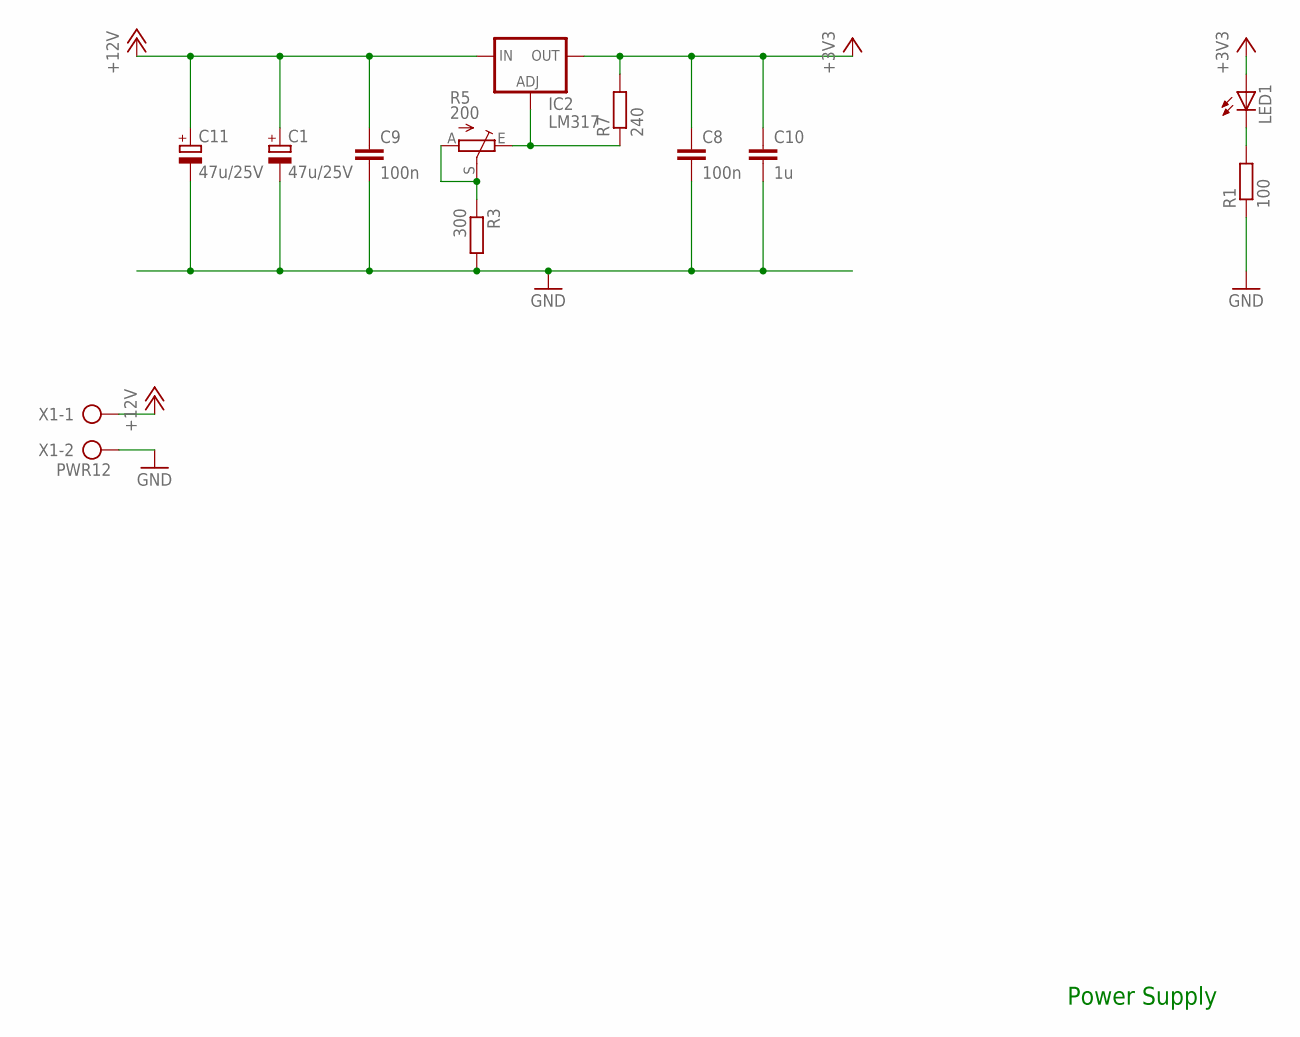
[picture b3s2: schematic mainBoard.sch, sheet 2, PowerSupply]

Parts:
C1, C11: 47u/25V; PANASONIC_D
C8, C9: 100n; C0805
C10: 1u; C0805
IC2: LM317; SOT223
LED1: LEDCHIP-LED0805; CHIP-LED0805
R1: 100; R0805
R3: 300; R0805
R5: 200; S64Y
R7: 240; R0805
X1: PWR12; AK500/2

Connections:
+3V3: C8.1, C10.1, IC2.4 (OUT), LED1.A, R7.2; also elsewhere on the board
+12V: C1.+, C9.1, C11.+, IC2.3 (IN), X1.1; also elsewhere on the board
GND: C1.-, C8.2, C9.2, C10.2, C11.-, R1.1, R3.2, X1.2; also elsewhere on the board
unnamed: LED1.C, R1.2
unnamed: R3.1, R5.A, R5.S
unnamed: IC2.1 (ADJ), R5.E, R7.1

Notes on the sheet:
Power Supply
